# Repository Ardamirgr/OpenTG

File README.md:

<div align="center">

# OpenTG

**Open-source automotive electronics for monitoring, control, ECU communication, and calibration.**

Originally developed for the **Hyundai Coupe / Tiburon**, with many projects designed to be adaptable to other vehicles, ECUs, and custom engine-management setups.

[Support OpenTG](https://www.paypal.com/donate/?hosted_button_id=CYKH5WKZKP4M2)

</div>

---

## Projects

### OpenTG AFR Meter

A complete wideband AFR/lambda system based on the **Bosch LSU 4.9** sensor and **Bosch CJ125** interface IC.

**Wideband controller**

- LSU 4.9 sensor and heater control
- CAN bus output
- Configurable analog AFR/lambda output
- Narrowband and wideband signal emulation

**Digital gauge**

- TFT display with AFR, lambda, oxygen concentration, and sensor-temperature views
- Configurable LED bar
- On-device menu and EEPROM-stored settings
- CAN communication with the controller

---

### OpenTG Boost Controller

A configurable electronic boost-control system for turbocharged vehicles using a MAC-style boost-control solenoid.

- Closed-loop boost control
- Boost targets by RPM and gear
- Multiple selectable boost profiles
- MAP and intake-air-temperature measurement
- CAN-based RPM and vehicle-speed input
- Optional analog inputs
- Overboost protection
- Exhaust-gas-temperature support
- Dedicated TFT gauge and user interface

---

### KLT120 K-Line / L-Line Transceiver

An open-source discrete automotive **K-Line / L-Line transceiver** designed for communication with ECUs and other diagnostic modules using **ISO 9141, ISO 14230 / KWP2000**, and manufacturer-specific K-Line protocols.

Unlike conventional designs based on dedicated K-Line transceiver ICs, the KLT120 uses **LM393B comparators** and discrete N-channel MOSFET line drivers.

Key features include:

* Automotive **K-Line** interface
* Automotive **L-Line** interface
* Independent K-Line and L-Line control
* Selectable **3.3V or 5V MCU logic** depending on the fitted LDO
* Direct interface with microcontroller UART peripherals
* Support for conventional **10.4 kbaud** diagnostic communication
* Support for **5-baud and fast initialization** methods
* Designed for reliable operation at **120 kbaud and beyond**
* Suitable for ECU diagnostics, flashing, logging, and reverse-engineering applications

---

### LTM43 Live Tuning Module

A live-calibration module designed specifically for the **Siemens SIMK43 ECU**.

The LTM43 replaces the original ECU flash memory with a removable module containing:

- **1 Mbit flash memory**, twice the capacity of the original 512 Kbit device
- **512 Kbit SRAM** connected in parallel with the flash memory
- A castellated pin-header adapter PCB that solders directly to the original flash footprint

> [!NOTE]
> The design is based on the live-calibration approach used by Siemens during ECU and engine development.

---

### SLCAN Adapter - Experimental

A compact CAN-to-USB serial interface for ECU flashing, diagnostics, logging, and calibration.

Typical uses include:

- SIMK43 communication
- ECU data logging
- CAN traffic monitoring
- LTM43 live tuning
- Use with compatible OpenTG and OpenGK tools

The adapter implements the **SLCAN protocol**, providing a low-cost alternative to commercial CAN interfaces for supported software.

---

### S4/RS4 MAF Adapter

An adapter board for integrating the Audi S4/RS4 B6 mass-airflow sensors with the stock SIMK43 ECU setups.

It provides a clean interface between the original harness connector and the MAF, without requiring any modifications.

Typical applications include:

- Turbo conversions
- Setups that exceed the measurement range of the original MAF sensor
- Replacement option if the stock MAF sensor can't be found from a reputable manufacturer (VDO, Continental).

---

### R8 COP Adapter

An ignition adapter board for converting the G4GC engines to Audi R8-style coil-on-plug ignition coils. This can theoretically work on any wasted-spark setup.

The board provides an organized interface between the factory engine harness and the replacement coils, simplifying wiring and installation.

> [!IMPORTANT]
> Coil compatibility and ignition strategy must be verified before installation. Depending on the ECU, the ignition dwell times WILL need to be changed, or the R8 Coils will be catastrophically damaged.
> For the G4GC dwell times of <2ms should be used. For most turbocharged setups 1.4-1.6ms is enough.

---

### Oil Temperature / Oil Pressure Gauge

A planned standalone gauge for monitoring engine-oil temperature and pressure.

**Status:** Under development. Have a prototype made from a modified Gauge unit, but no proper hardware design.

---

## Repository Contents

Depending on the project, each directory may include:

| Category | Contents |
|---|---|
| **Hardware** | Schematics, PCB layouts, Gerbers, BOMs, and assembly notes |
| **Firmware** | Embedded source code, binaries, and flashing instructions |
| **Wiring** | Pinouts, connection diagrams, and installation guidance |
| **Calibration** | Configuration files, lookup data, and setup notes |
| **Mechanical** | Enclosure, mounting, or other fabrication files |

Refer to the README inside each project directory for project-specific instructions.

---

## Intended Use

OpenTG projects are intended for enthusiasts, developers, motorsport applications, research, and education.

They may require fine-pitch soldering, ECU disassembly, firmware flashing, automotive electrical knowledge, and engine-management calibration experience.

> [!WARNING]
> Incorrect installation, wiring, firmware, or calibration can damage the ECU, engine, sensors, wiring, or connected equipment. Verify pin assignments, supply voltages, grounding, firmware versions, and board revisions before powering any hardware.

---

## Contributing

Contributions, testing, bug reports, documentation improvements, and hardware revisions are welcome.

For useful bug reports, include the relevant hardware revision, firmware version or commit, vehicle and ECU type, wiring configuration, CAN bitrate, logs or measurements, and a clear description of the problem.

---

## License

See the LICENSE file present in the repository root for license information.

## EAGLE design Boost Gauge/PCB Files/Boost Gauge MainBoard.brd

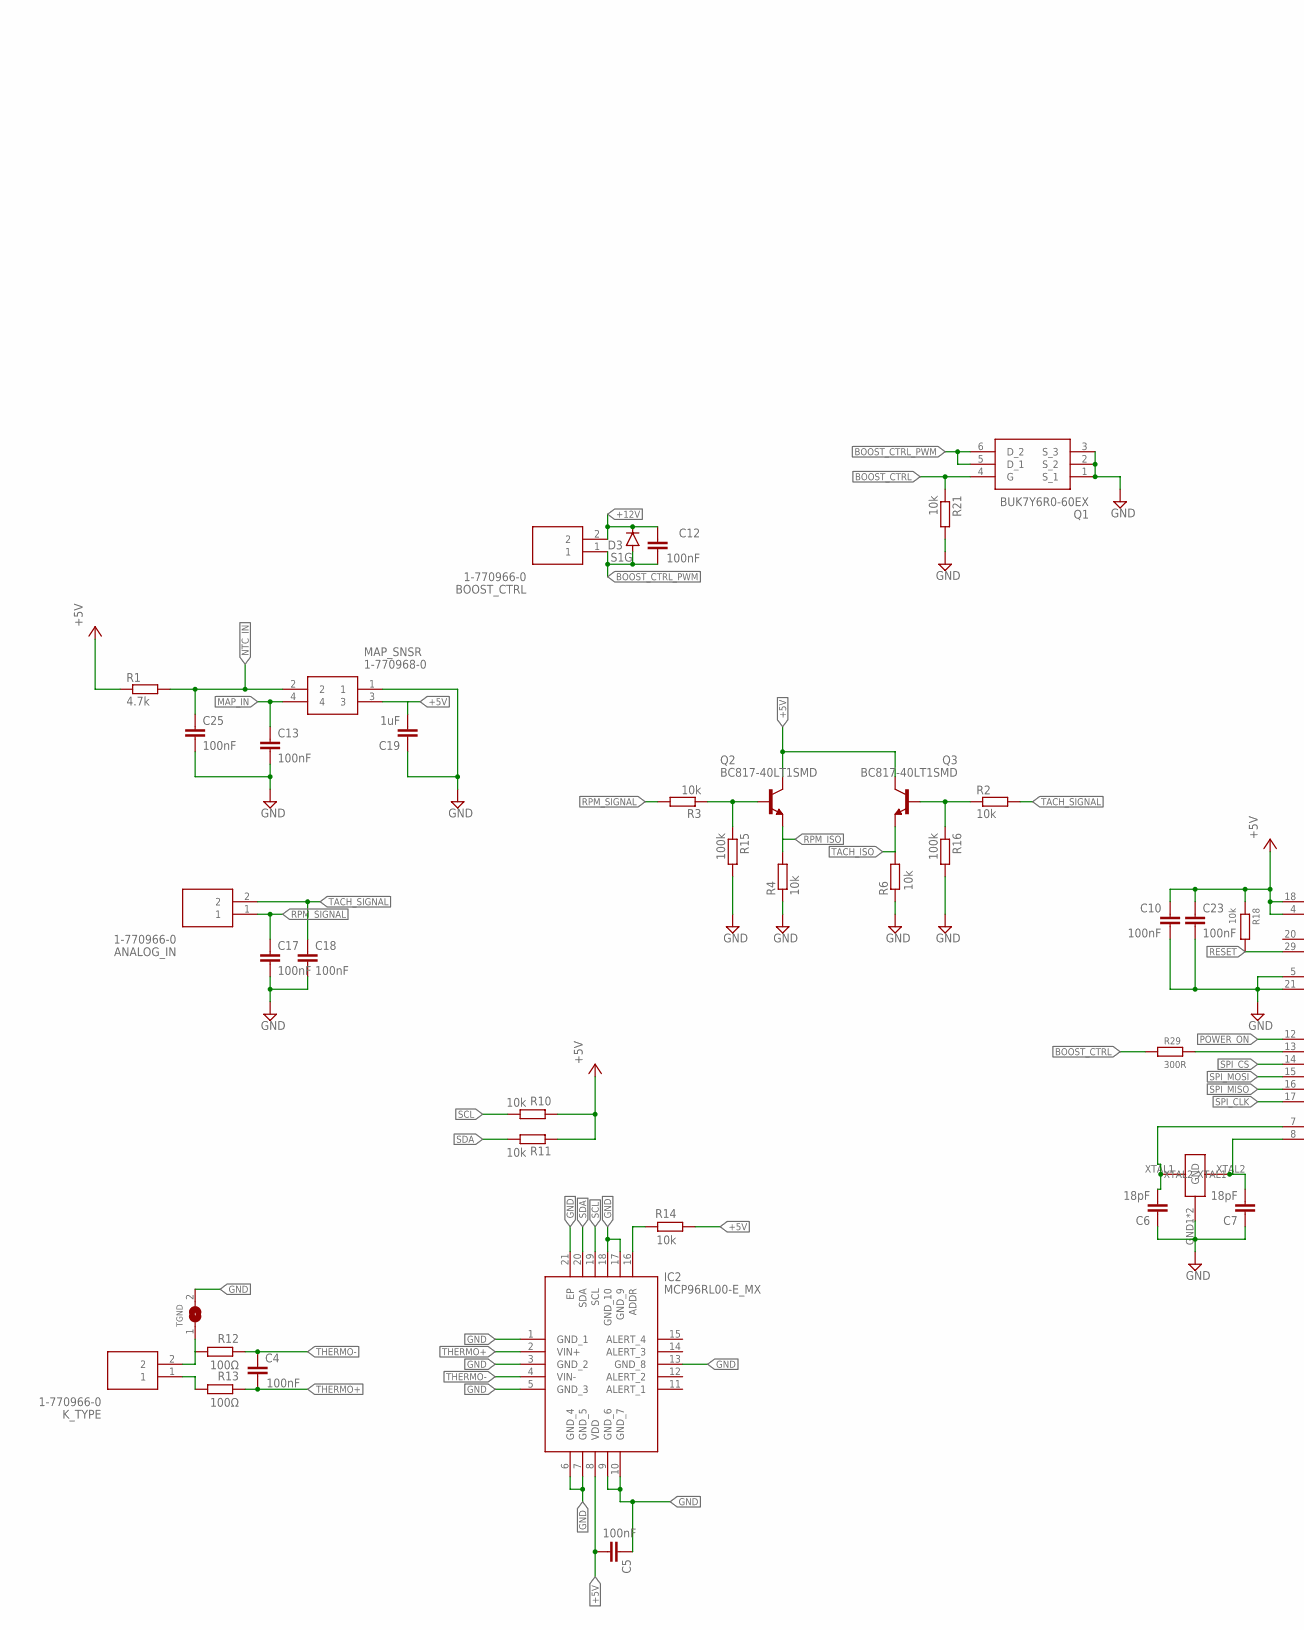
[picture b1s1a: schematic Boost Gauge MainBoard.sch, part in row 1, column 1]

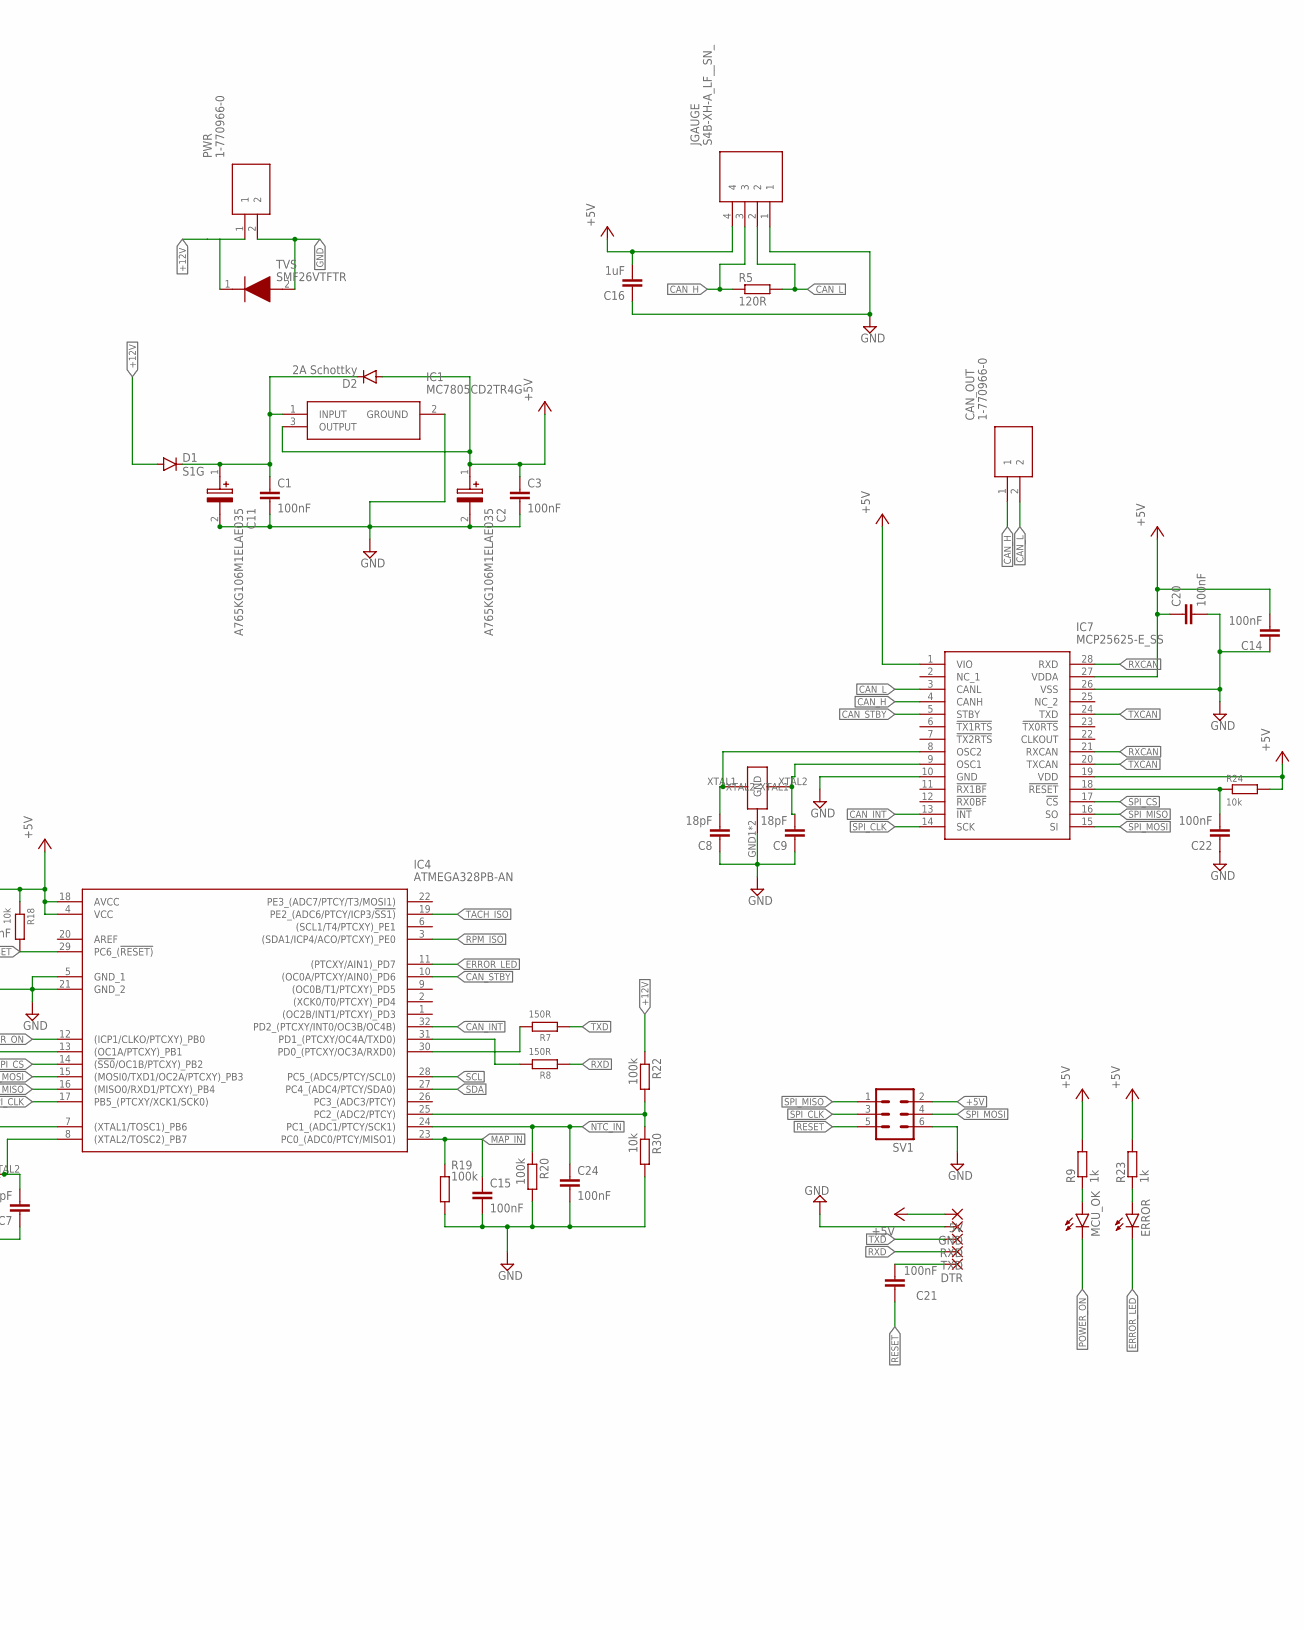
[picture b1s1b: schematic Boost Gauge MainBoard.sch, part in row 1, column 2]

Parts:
5V: 1,6/0,9
ANALOG_IN: 1-770966-0; 17709660
BOOST_CTRL: 1-770966-0; 17709660
C1, C3, C4, C5, C10, C12, C13, C14, C15, C17, C18, C20, C21, C22, C23, C24, C25: 100nF; C0805
C2, C11: A765KG106M1ELAE035; CAPAE830X730N
C6, C7, C8, C9: 18pF; C0805
C16, C19: 1uF; C0805
CAN_OUT: 1-770966-0; 17709660
D1, D3: S1G; DO-214AC
D2: 2A Schottky; DO-214AC
DTR: 1,6/0,9
ERROR: LEDCHIPLED_1206; CHIPLED_1206
GND: 1,6/0,9
IC1: MC7805CD2TR4G
IC2: MCP96RL00-E_MX; QFN65P500X500X100-21N
IC4: ATMEGA328PB-AN; QFP80P900X900X120-32N
IC7: MCP25625-E_SS; SOP65P780X200-28N
JGAUGE: S4B-XH-A_LF__SN_; S4BXHALFSN
K_TYPE: 1-770966-0; 17709660
MAP_SNSR: 1-770968-0; 17709680
MCU_OK: LEDCHIPLED_1206; CHIPLED_1206
PWR: 1-770966-0; 17709660
Q1: BUK7Y6R0-60EX; BUK7Y6R060EX
Q2, Q3: BC817-40LT1SMD; SOT23-BEC
R1: 4.7k; R0805
R2, R3, R4, R6, R10, R11, R14, R18, R21, R24, R30: 10k; R0805
R5: 120R; R1206
R7, R8: 150R; R0805
R9, R23: 1k; R0805
R12, R13: 100Ω; R0805
R15, R16, R19, R20, R22: 100k; R0805
R29: 300R; R0805
RXD: 1,6/0,9
SV1: MA03-2
TGND: SOLDERJUMPER; SOLDERJUMPER_ARROW_NOPASTE
TVS: SMF26VTFTR
TXD: 1,6/0,9
U$4, U$5: E3X160181X04

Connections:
+5V: 5V.1, C2.1 (+), C3.1, C5.2, C10.1, C14.2, C16.2, C19.2, C20.1, C23.1, D2.A, IC1.3 (OUTPUT), IC2.8 (VDD), IC4.4 (VCC), IC4.18 (AVCC), IC7.1 (VIO), IC7.19 (VDD), IC7.27 (VDDA), JGAUGE.4, MAP_SNSR.3, Q2.C, Q3.C, R1.1, R9.2, R10.1, R11.1, R14.1, R18.1, R23.2, R24.2, SV1.2
+12V: BOOST_CTRL.2, C12.2, D1.A, D3.C, PWR.1, R22.1, TVS.1 (K)
BOOST_CTRL: Q1.4 (G), R21.1, R29.1
BOOST_CTRL_PWM: BOOST_CTRL.1, C12.1, D3.A, Q1.5 (D_1), Q1.6 (D_2)
CAN_H: CAN_OUT.1, IC7.4 (CANH), JGAUGE.3, R5.1
CAN_INT: IC4.32 (PD2_(PTCXY/INT0/OC3B/OC4B)), IC7.13 (!INT)
CAN_L: CAN_OUT.2, IC7.3 (CANL), JGAUGE.2, R5.2
CAN_STBY: IC4.10 ((OC0A/PTCXY/AIN0)_PD6), IC7.5 (STBY)
DTR: C21.2, DTR.1
ERROR_LED: ERROR.C, IC4.11 ((PTCXY/AIN1)_PD7)
GND: C1.2, C2.2 (-), C3.2, C5.1, C6.1, C7.1, C8.1, C9.1, C10.2, C11.2 (-), C13.2, C14.1, C15.2, C16.1, C17.2, C18.2, C19.1, C20.2, C22.1, C23.2, C24.2, C25.2, GND.1, IC1.2 (GROUND), IC2.1 (GND_1), IC2.3 (GND_2), IC2.5 (GND_3), IC2.6 (GND_4), IC2.7 (GND_5), IC2.9 (GND_6), IC2.10 (GND_7), IC2.13 (GND_8), IC2.17 (GND_9), IC2.18 (GND_10), IC2.21 (EP), IC4.5 (GND_1), IC4.21 (GND_2), IC7.10 (GND), IC7.26 (VSS), JGAUGE.1, MAP_SNSR.1, PWR.2, Q1.1 (S_1), Q1.2 (S_2), Q1.3 (S_3), R4.1, R6.1, R15.2, R16.2, R19.2, R20.2, R21.2, R30.2, SV1.6, TGND.2, TVS.2 (A), U$4.GND1 (GND), U$4.GND2 (GND), U$5.GND1 (GND), U$5.GND2 (GND)
MAP_IN: C13.1, C15.1, IC4.23 (PC0_(ADC0/PTCY/MISO1)), MAP_SNSR.4, R19.1
unnamed: C9.2, IC7.9 (OSC1), U$5.XTAL2
unnamed: Q2.B, R3.1, R15.1
unnamed: Q3.B, R2.1, R16.1
unnamed: C8.2, IC7.8 (OSC2), U$5.XTAL1
unnamed: C1.1, C11.1 (+), D1.C, D2.C, IC1.1 (INPUT)
unnamed: IC4.31 (PD1_(PTCXY/OC4A/TXD0)), R8.2
unnamed: IC4.30 (PD0_(PTCXY/OC3A/RXD0)), R7.2
unnamed: MCU_OK.A, R9.1
unnamed: K_TYPE.1, R13.2
unnamed: ERROR.A, R23.1
unnamed: C22.2, IC7.18 (!RESET), R24.1
unnamed: IC2.16 (ADDR), R14.2
unnamed: IC4.25 (PC2_(ADC2/PTCY)), R22.2, R30.1
unnamed: C7.2, IC4.8 ((XTAL2/TOSC2)_PB7), U$4.XTAL2
unnamed: C6.2, IC4.7 ((XTAL1/TOSC1)_PB6), U$4.XTAL1
unnamed: IC4.13 ((OC1A/PTCXY)_PB1), R29.2
NTC_IN: C24.1, C25.1, IC4.24 (PC1_(ADC1/PTCY/SCK1)), MAP_SNSR.2, R1.2, R20.1
POWER_ON: IC4.12 ((ICP1/CLKO/PTCXY)_PB0), MCU_OK.C
RESET: C21.1, IC4.29 (PC6_(!RESET)), R18.2, SV1.5
RPM_ISO: IC4.3 ((SDA1/ICP4/ACO/PTCXY)_PE0), Q2.E, R4.2
RPM_SIGNAL: ANALOG_IN.1, C17.1, R3.2
RXCAN: IC7.21 (RXCAN), IC7.28 (RXD)
RXD: R8.1, TXD.1
SCL: IC2.19 (SCL), IC4.28 (PC5_(ADC5/PTCY/SCL0)), R10.2
SDA: IC2.20 (SDA), IC4.27 (PC4_(ADC4/PTCY/SDA0)), R11.2
SPI_CLK: IC4.17 (PB5_(PTCXY/XCK1/SCK0)), IC7.14 (SCK), SV1.3
SPI_CS: IC4.14 ((!SS0!/OC1B/PTCXY)_PB2), IC7.17 (!CS)
SPI_MISO: IC4.16 ((MISO0/RXD1/PTCXY)_PB4), IC7.16 (SO), SV1.1
SPI_MOSI: IC4.15 ((MOSI0/TXD1/OC2A/PTCXY)_PB3), IC7.15 (SI), SV1.4
TACH_ISO: IC4.19 (PE2_(ADC6/PTCY/ICP3/!SS1)), Q3.E, R6.2
TACH_SIGNAL: ANALOG_IN.2, C18.1, R2.2
THERMO+: C4.2, IC2.2 (VIN+), R13.1
THERMO-: C4.1, IC2.4 (VIN-), R12.1
THERMO-1: K_TYPE.2, R12.2, TGND.1
TXCAN: IC7.20 (TXCAN), IC7.24 (TXD)
TXD: R7.1, RXD.1

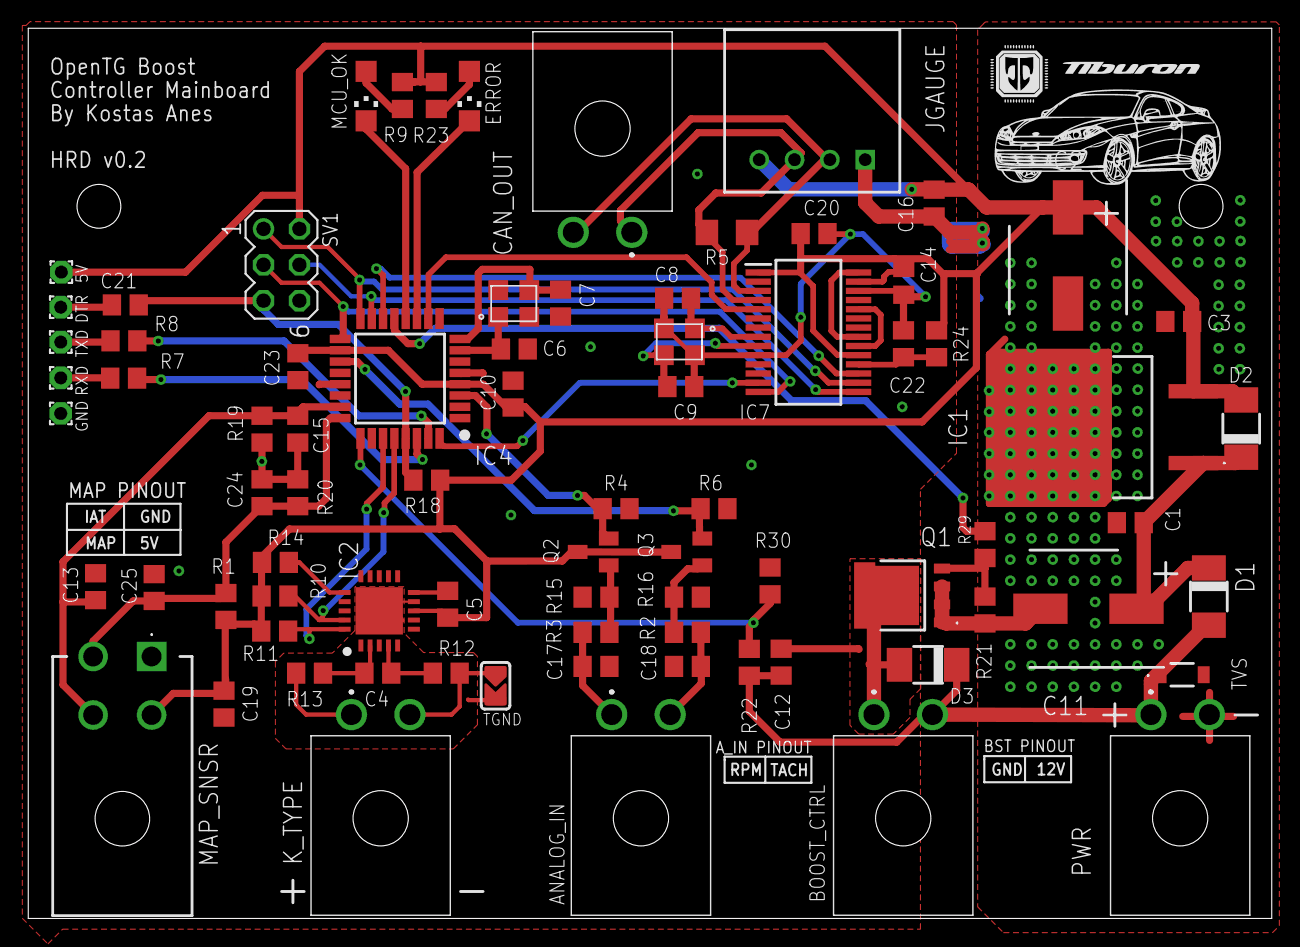
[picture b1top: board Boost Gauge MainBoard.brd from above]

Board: 2 copper layers, 88.0 x 63.0 mm, 79 parts (0 on the bottom side), 48 nets.

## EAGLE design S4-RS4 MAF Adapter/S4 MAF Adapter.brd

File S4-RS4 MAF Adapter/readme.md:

# Bosch MAF Sensor Adapter Board

PCB files for an adapter board compatible with the following Bosch MAF sensors:

- Bosch `0280218038`
- Bosch `028021807D`
- Bosch `0280218067`
- Bosch `0986280219`
- Bosch `028021808P`

## Connectors

The connector that mates to the ECU harness can typically be found under the part name `HD052H-3.5-11` on sites such as AliExpress or Alibaba.

The connector that mates to the Bosch MAF sensors is `1J0973775A`.

## Notes

### TVS and Reverse-Polarity Protection

The TVS diode and reverse-polarity diode are optional. They were included for extra protection, but they are not required for normal operation.

If you choose not to install the reverse-polarity diode, short the `D1` pads.

### Chassis Ground Jumper

Leave the jumper between **Chassis Ground** and the **ground pour** open.

This jumper is included only for debugging. Closing it shorts chassis ground to sensor ground and may negatively affect signal integrity for all ECU sensors.

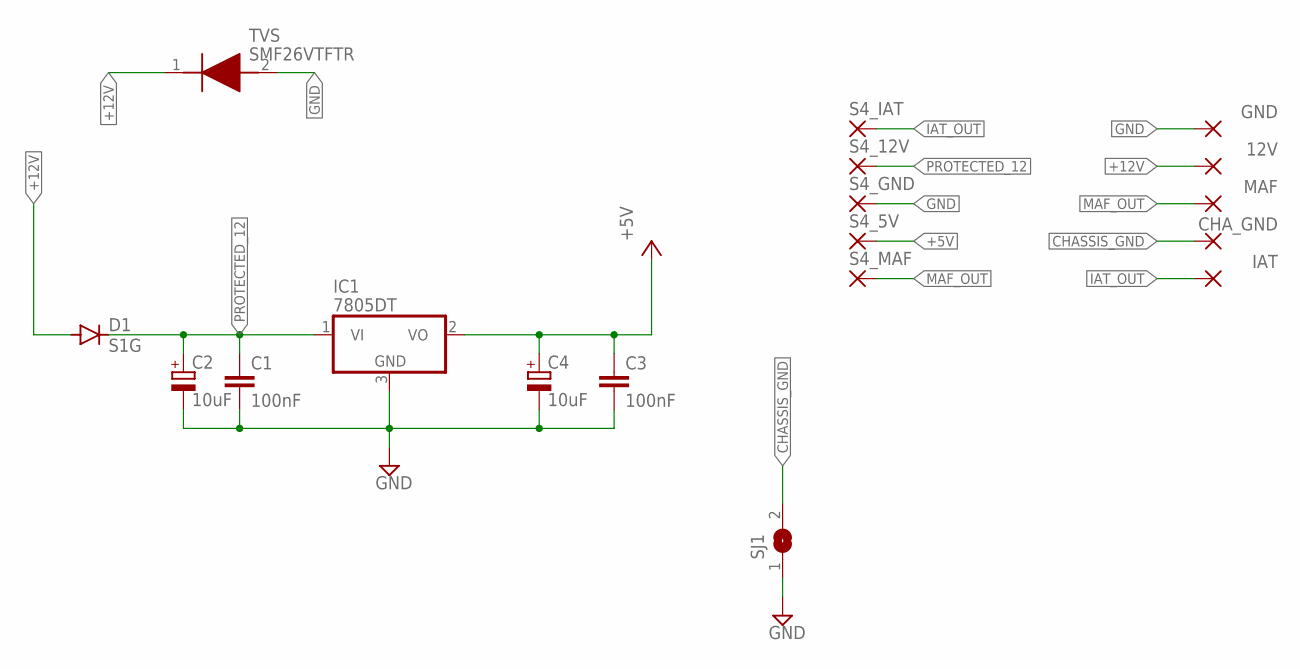
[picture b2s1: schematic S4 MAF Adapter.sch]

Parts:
12V: 2,54/1,1
C1, C3: 100nF; C0805
C2, C4: 10uF; E2-5
CHA_GND: 2,54/1,1
D1: S1G; DO-214AC
GND: 2,54/1,1
IAT: 2,54/1,1
IC1: 7805DT; TO252
MAF: 2,54/1,1
S4_5V, S4_12V, S4_GND, S4_IAT, S4_MAF: 2,54/1,1
SJ1: SJ
TVS: SMF26VTFTR

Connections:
+5V: C3.1, C4.+, IC1.2 (VO), S4_5V.1
+12V: 12V.1, D1.A, TVS.1 (K)
CHASSIS_GND: CHA_GND.1, SJ1.2
GND: C1.2, C2.-, C3.2, C4.-, GND.1, IC1.3 (GND), S4_GND.1, SJ1.1, TVS.2 (A)
IAT_OUT: IAT.1, S4_IAT.1
MAF_OUT: MAF.1, S4_MAF.1
PROTECTED_12: C1.1, C2.+, D1.C, IC1.1 (VI), S4_12V.1

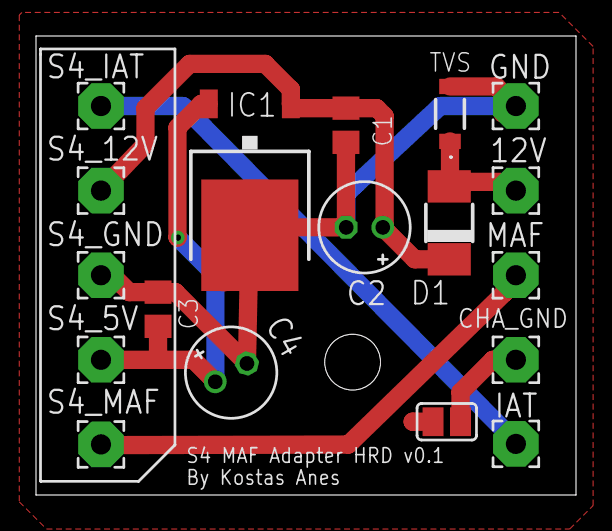
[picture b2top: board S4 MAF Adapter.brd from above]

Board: 2 copper layers, 30.0 x 25.5 mm, 18 parts (0 on the bottom side), 7 nets.

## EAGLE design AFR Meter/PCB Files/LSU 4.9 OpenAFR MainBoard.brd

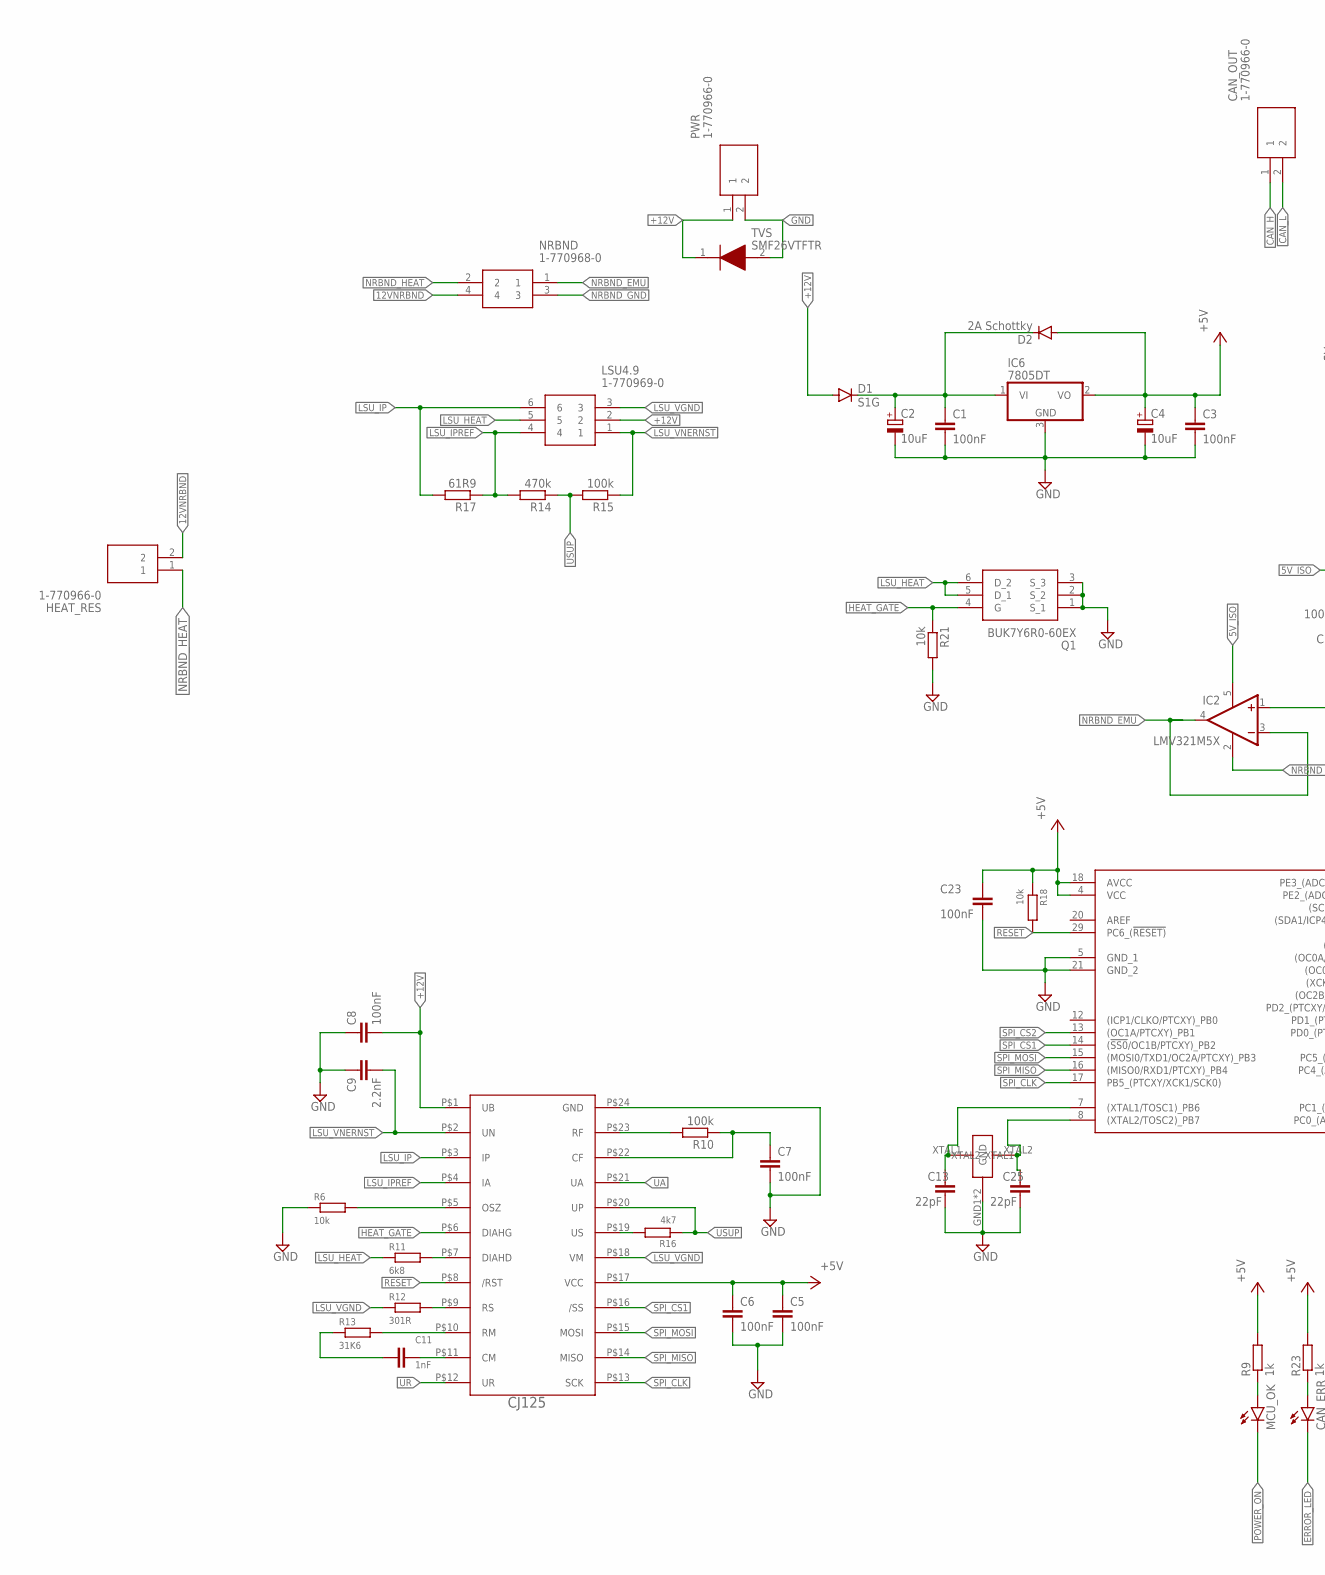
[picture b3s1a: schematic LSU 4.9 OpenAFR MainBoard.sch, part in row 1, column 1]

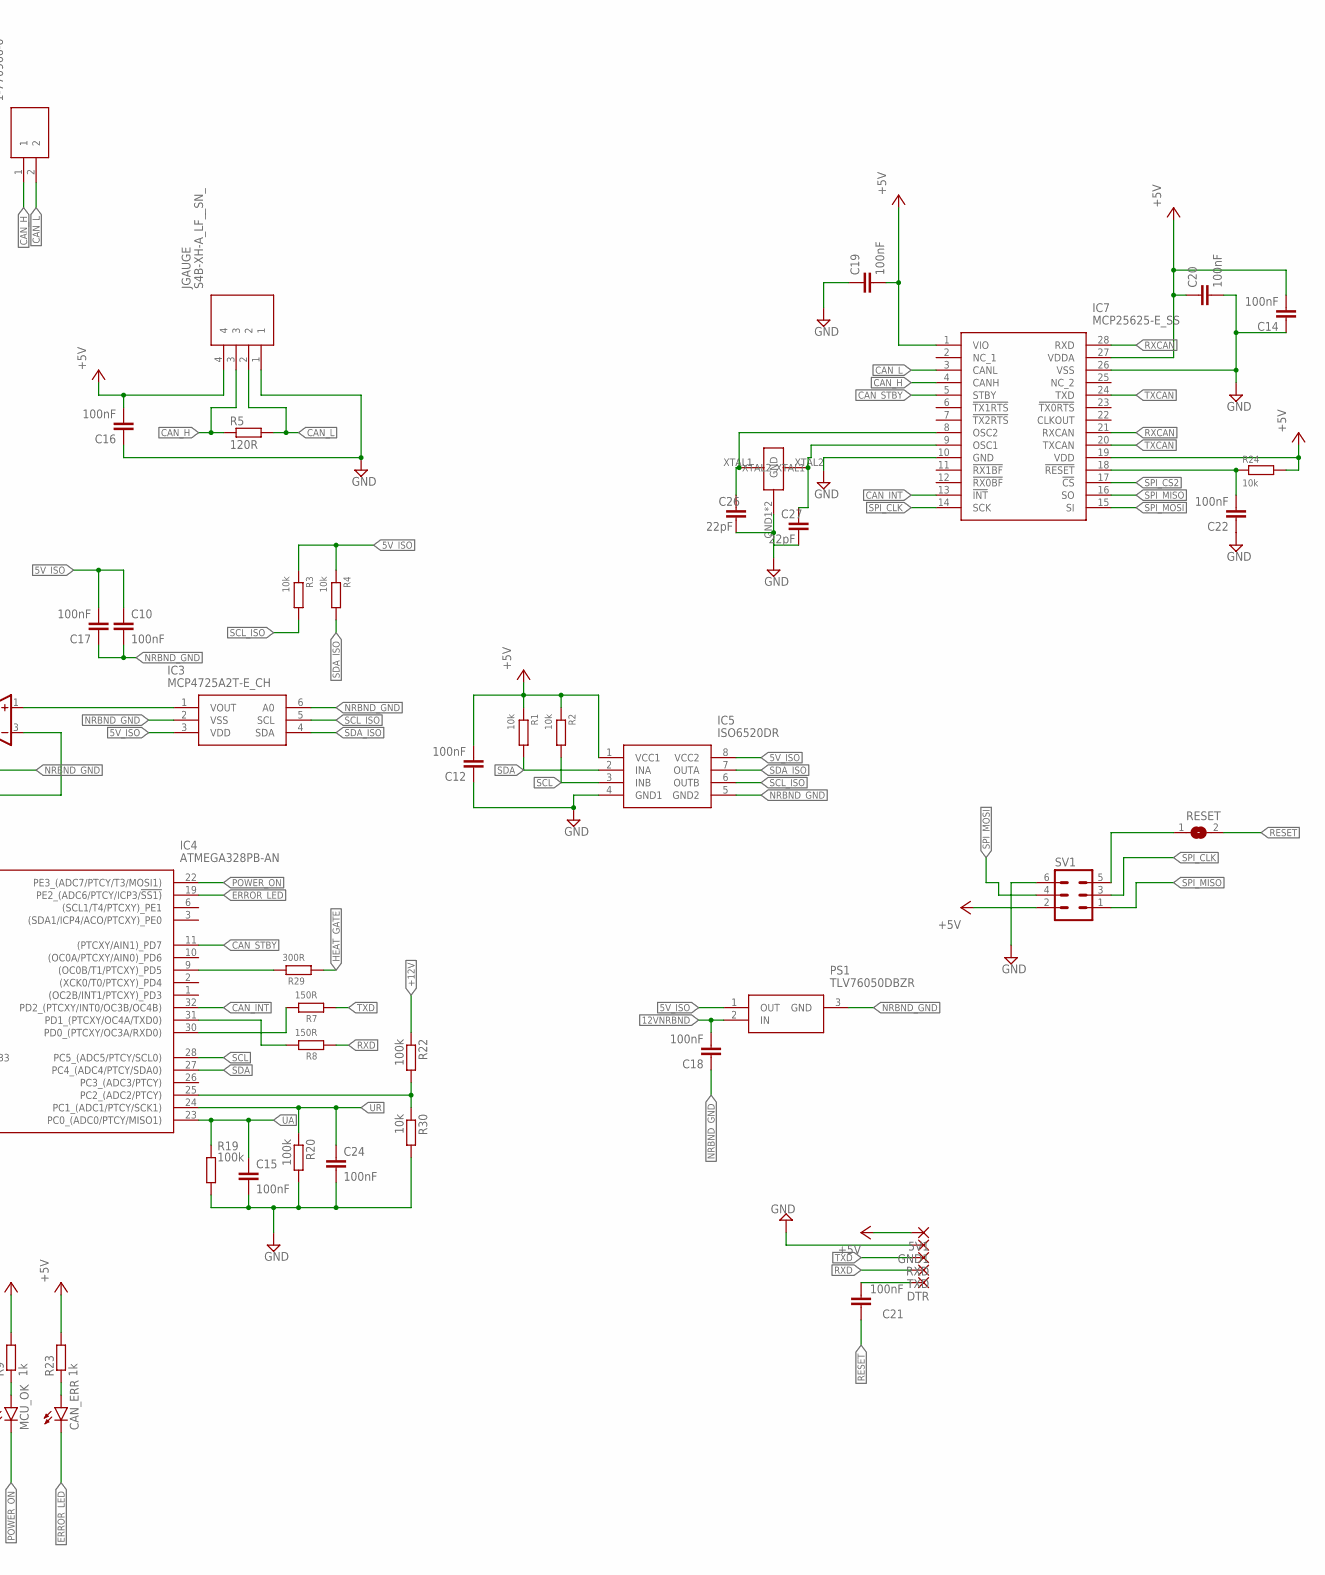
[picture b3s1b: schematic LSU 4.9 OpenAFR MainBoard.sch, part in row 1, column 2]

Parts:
5V1: 1,6/0,9
C1, C3, C5, C6, C7, C8, C10, C12, C14, C15, C16, C17, C18, C19, C20, C21, C22, C23, C24: 100nF; C0805
C2, C4: 10uF; UD-5X5,8_NICHICON
C9: 2.2nF; C0805
C11: 1nF; C0805
C13, C25, C26, C27: 22pF; C0805
CAN_ERR: LEDCHIPLED_1206; CHIPLED_1206
CAN_OUT: 1-770966-0; 17709660
D1: S1G; DO-214AC
D2: 2A Schottky; DO-214AC
DTR: 1,6/0,9
GND1: 1,6/0,9
HEAT_RES: 1-770966-0; 17709660
IC2: LMV321M5X; SOT23-5
IC3: MCP4725A2T-E_CH; SOT95P270X145-6N
IC4: ATMEGA328PB-AN; QFP80P900X900X120-32N
IC5: ISO6520DR; SOIC127P600X175-8N
IC6: 7805DT; TO252
IC7: MCP25625-E_SS; SOP65P780X200-28N
JGAUGE: S4B-XH-A_LF__SN_; S4BXHALFSN
LSU4.9: 1-770969-0; 17709690
MCU_OK: LEDCHIPLED_1206; CHIPLED_1206
NRBND: 1-770968-0; 17709680
PS1: TLV76050DBZR; SOT95P237X112-3N
PWR: 1-770966-0; 17709660
Q1: BUK7Y6R0-60EX; BUK7Y6R060EX
R1, R2, R3, R4, R6, R18, R21, R24, R30: 10k; R0805
R5: 120R; R1206
R7, R8: 150R; R0805
R9, R23: 1k; R0805
R10, R15, R19, R20, R22: 100k; R0805
R11: 6k8; R0805
R12: 301R; R0805
R13: 31K6; R0805
R14: 470k; R0805
R16: 4k7; R0805
R17: 61R9; R0805
R29: 300R; R0805
RESET: SJ
RXD: 1,6/0,9
SV1: MA03-2
TVS: SMF26VTFTR
TXD: 1,6/0,9
U$1: CJ125-SOIC24
U$4, U$5: E3X160181X04

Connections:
5V_ISO: C10.1, C17.2, IC2.5 (V+), IC3.3 (VDD), IC5.8 (VCC2), PS1.1 (OUT), R3.1, R4.1
12VNRBND: C18.2, HEAT_RES.2, NRBND.4, PS1.2 (IN)
+5V: 5V1.1, C3.1, C4.+, C5.1, C6.1, C12.2, C14.2, C16.2, C19.2, C20.1, C23.1, D2.A, IC4.4 (VCC), IC4.18 (AVCC), IC5.1 (VCC1), IC6.2 (VO), IC7.1 (VIO), IC7.19 (VDD), IC7.27 (VDDA), JGAUGE.4, R1.1, R2.1, R9.2, R18.1, R23.2, R24.2, SV1.2, U$1.P$17 (VCC)
+12V: C8.2, D1.A, LSU4.9.2, PWR.1, R22.1, TVS.1 (K), U$1.P$1 (UB)
CAN_H: CAN_OUT.1, IC7.4 (CANH), JGAUGE.3, R5.1
CAN_INT: IC4.32 (PD2_(PTCXY/INT0/OC3B/OC4B)), IC7.13 (!INT)
CAN_L: CAN_OUT.2, IC7.3 (CANL), JGAUGE.2, R5.2
CAN_STBY: IC4.11 ((PTCXY/AIN1)_PD7), IC7.5 (STBY)
DTR: C21.2, DTR.1
ERROR_LED: CAN_ERR.C, IC4.19 (PE2_(ADC6/PTCY/ICP3/!SS1))
GND: C1.2, C2.-, C3.2, C4.-, C5.2, C6.2, C7.2, C8.1, C9.2, C12.1, C13.2, C14.1, C15.2, C16.1, C19.1, C20.2, C22.1, C23.2, C24.2, C25.2, C26.2, C27.2, GND1.1, IC4.5 (GND_1), IC4.21 (GND_2), IC5.4 (GND1), IC6.3 (GND), IC7.10 (GND), IC7.26 (VSS), JGAUGE.1, PWR.2, Q1.1 (S_1), Q1.2 (S_2), Q1.3 (S_3), R6.1, R19.2, R20.2, R21.2, R30.2, SV1.6, TVS.2 (A), U$1.P$24 (GND), U$4.GND1 (GND), U$4.GND2 (GND), U$5.GND1 (GND), U$5.GND2 (GND)
HEAT_GATE: Q1.4 (G), R21.1, R29.1, U$1.P$6 (DIAHG)
LSU_HEAT: LSU4.9.5, Q1.5 (D_1), Q1.6 (D_2), R11.1
LSU_IP: LSU4.9.6, R17.2, U$1.P$3 (IP)
LSU_IPREF: LSU4.9.4, R14.2, R17.1, U$1.P$4 (IA)
LSU_VGND: LSU4.9.3, R12.1, U$1.P$18 (VM)
LSU_VNERNST: C9.1, LSU4.9.1, R15.1, U$1.P$2 (UN)
unnamed: C27.1, IC7.9 (OSC1), U$5.XTAL2
unnamed: R10.2, U$1.P$23 (RF)
unnamed: IC2.1 (+IN), IC3.1 (VOUT)
unnamed: C26.1, IC7.8 (OSC2), U$5.XTAL1
unnamed: C1.1, C2.+, D1.C, D2.C, IC6.1 (VI)
unnamed: R6.2, U$1.P$5 (OSZ)
unnamed: IC4.31 (PD1_(PTCXY/OC4A/TXD0)), R8.2
unnamed: IC4.30 (PD0_(PTCXY/OC3A/RXD0)), R7.2
unnamed: MCU_OK.A, R9.1
unnamed: C7.1, R10.1, U$1.P$22 (CF)
unnamed: CAN_ERR.A, R23.1
unnamed: C22.2, IC7.18 (!RESET), R24.1
unnamed: R12.2, U$1.P$9 (RS)
unnamed: R11.2, U$1.P$7 (DIAHD)
unnamed: R13.2, U$1.P$10 (RM)
unnamed: C11.1, R13.1
unnamed: C11.2, U$1.P$11 (CM)
unnamed: R16.2, U$1.P$19 (US)
unnamed: IC4.25 (PC2_(ADC2/PTCY)), R22.2, R30.1
unnamed: C25.1, IC4.8 ((XTAL2/TOSC2)_PB7), U$4.XTAL2
unnamed: C13.1, IC4.7 ((XTAL1/TOSC1)_PB6), U$4.XTAL1
unnamed: IC4.9 ((OC0B/T1/PTCXY)_PD5), R29.2
NRBND_EMU: IC2.3 (-IN), IC2.4 (OUT), NRBND.1
NRBND_GND: C10.2, C17.1, C18.1, IC2.2 (V-), IC3.2 (VSS), IC3.6 (A0), IC5.5 (GND2), NRBND.3, PS1.3 (GND)
NRBND_HEAT: HEAT_RES.1, NRBND.2
POWER_ON: IC4.22 (PE3_(ADC7/PTCY/T3/MOSI1)), MCU_OK.C
RESET: C21.1, IC4.29 (PC6_(!RESET)), R18.2, RESET.1, RESET.2, SV1.5, U$1.P$8 (/RST)
RXCAN: IC7.21 (RXCAN), IC7.28 (RXD)
RXD: R8.1, TXD.1
SCL: IC4.28 (PC5_(ADC5/PTCY/SCL0)), IC5.3 (INB), R2.2
SCL_ISO: IC3.5 (SCL), IC5.6 (OUTB), R3.2
SDA: IC4.27 (PC4_(ADC4/PTCY/SDA0)), IC5.2 (INA), R1.2
SDA_ISO: IC3.4 (SDA), IC5.7 (OUTA), R4.2
SPI_CLK: IC4.17 (PB5_(PTCXY/XCK1/SCK0)), IC7.14 (SCK), SV1.3, U$1.P$13 (SCK)
SPI_CS1: IC4.14 ((!SS0!/OC1B/PTCXY)_PB2), U$1.P$16 (/SS)
SPI_CS2: IC4.13 ((OC1A/PTCXY)_PB1), IC7.17 (!CS)
SPI_MISO: IC4.16 ((MISO0/RXD1/PTCXY)_PB4), IC7.16 (SO), SV1.1, U$1.P$14 (MISO)
SPI_MOSI: IC4.15 ((MOSI0/TXD1/OC2A/PTCXY)_PB3), IC7.15 (SI), SV1.4, U$1.P$15 (MOSI)
TXCAN: IC7.20 (TXCAN), IC7.24 (TXD)
TXD: R7.1, RXD.1
UA: C15.1, IC4.23 (PC0_(ADC0/PTCY/MISO1)), R19.1, U$1.P$21 (UA)
UR: C24.1, IC4.24 (PC1_(ADC1/PTCY/SCK1)), R20.1, U$1.P$12 (UR)
USUP: R14.1, R15.2, R16.1, U$1.P$20 (UP)

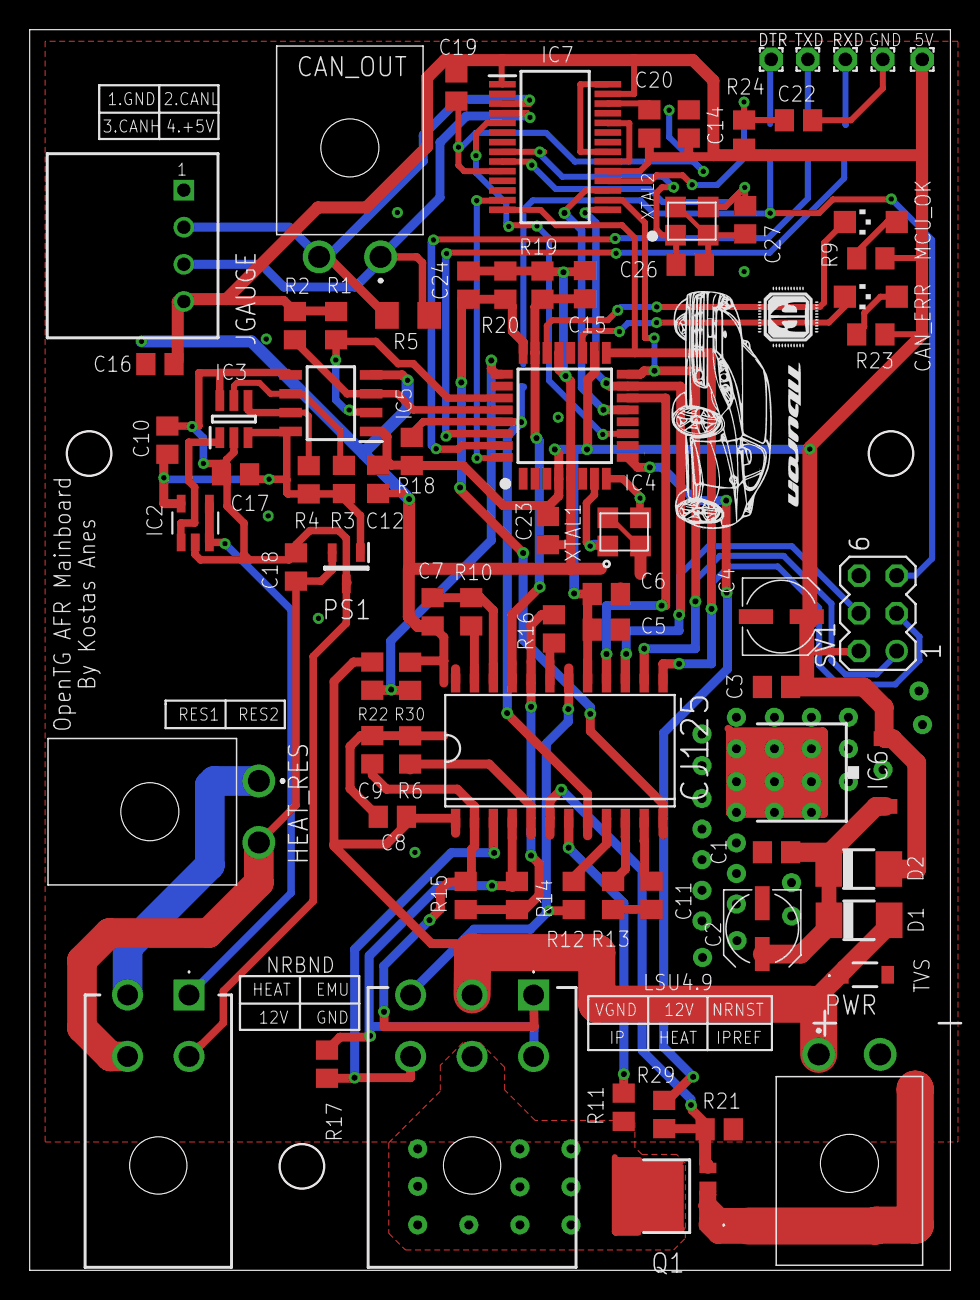
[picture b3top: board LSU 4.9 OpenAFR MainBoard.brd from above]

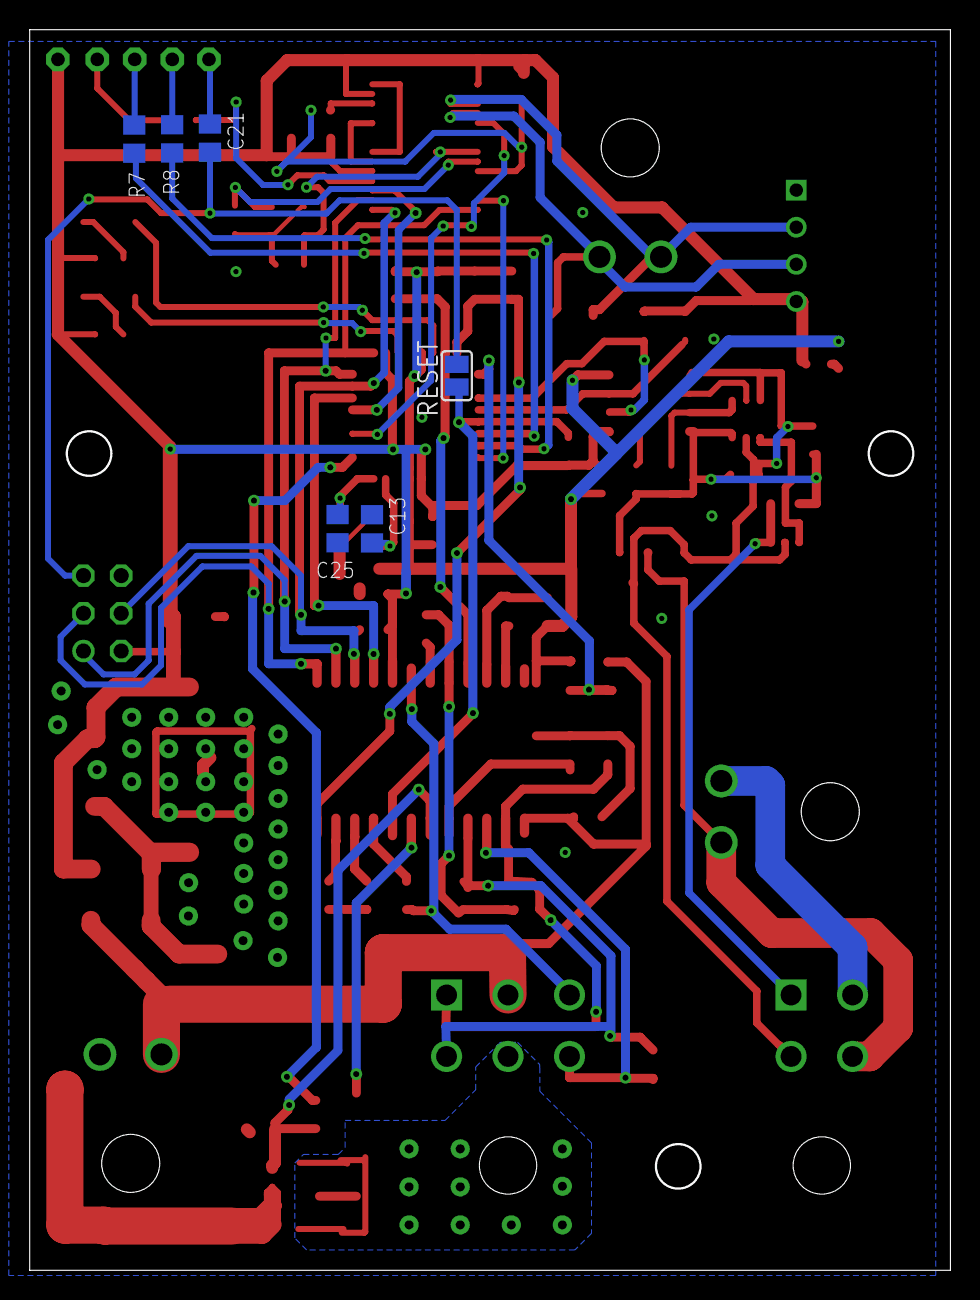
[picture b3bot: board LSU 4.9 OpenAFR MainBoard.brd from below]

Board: 2 copper layers, 62.0 x 83.5 mm, 82 parts (6 on the bottom side), 60 nets.

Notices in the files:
Boost Controller/readme.md:
See the repository root for license information.
parts and their libraries:
microbuilder: This work is placed in the public domain, and may be freely used for commercial and non-commercial work with the following conditions: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
